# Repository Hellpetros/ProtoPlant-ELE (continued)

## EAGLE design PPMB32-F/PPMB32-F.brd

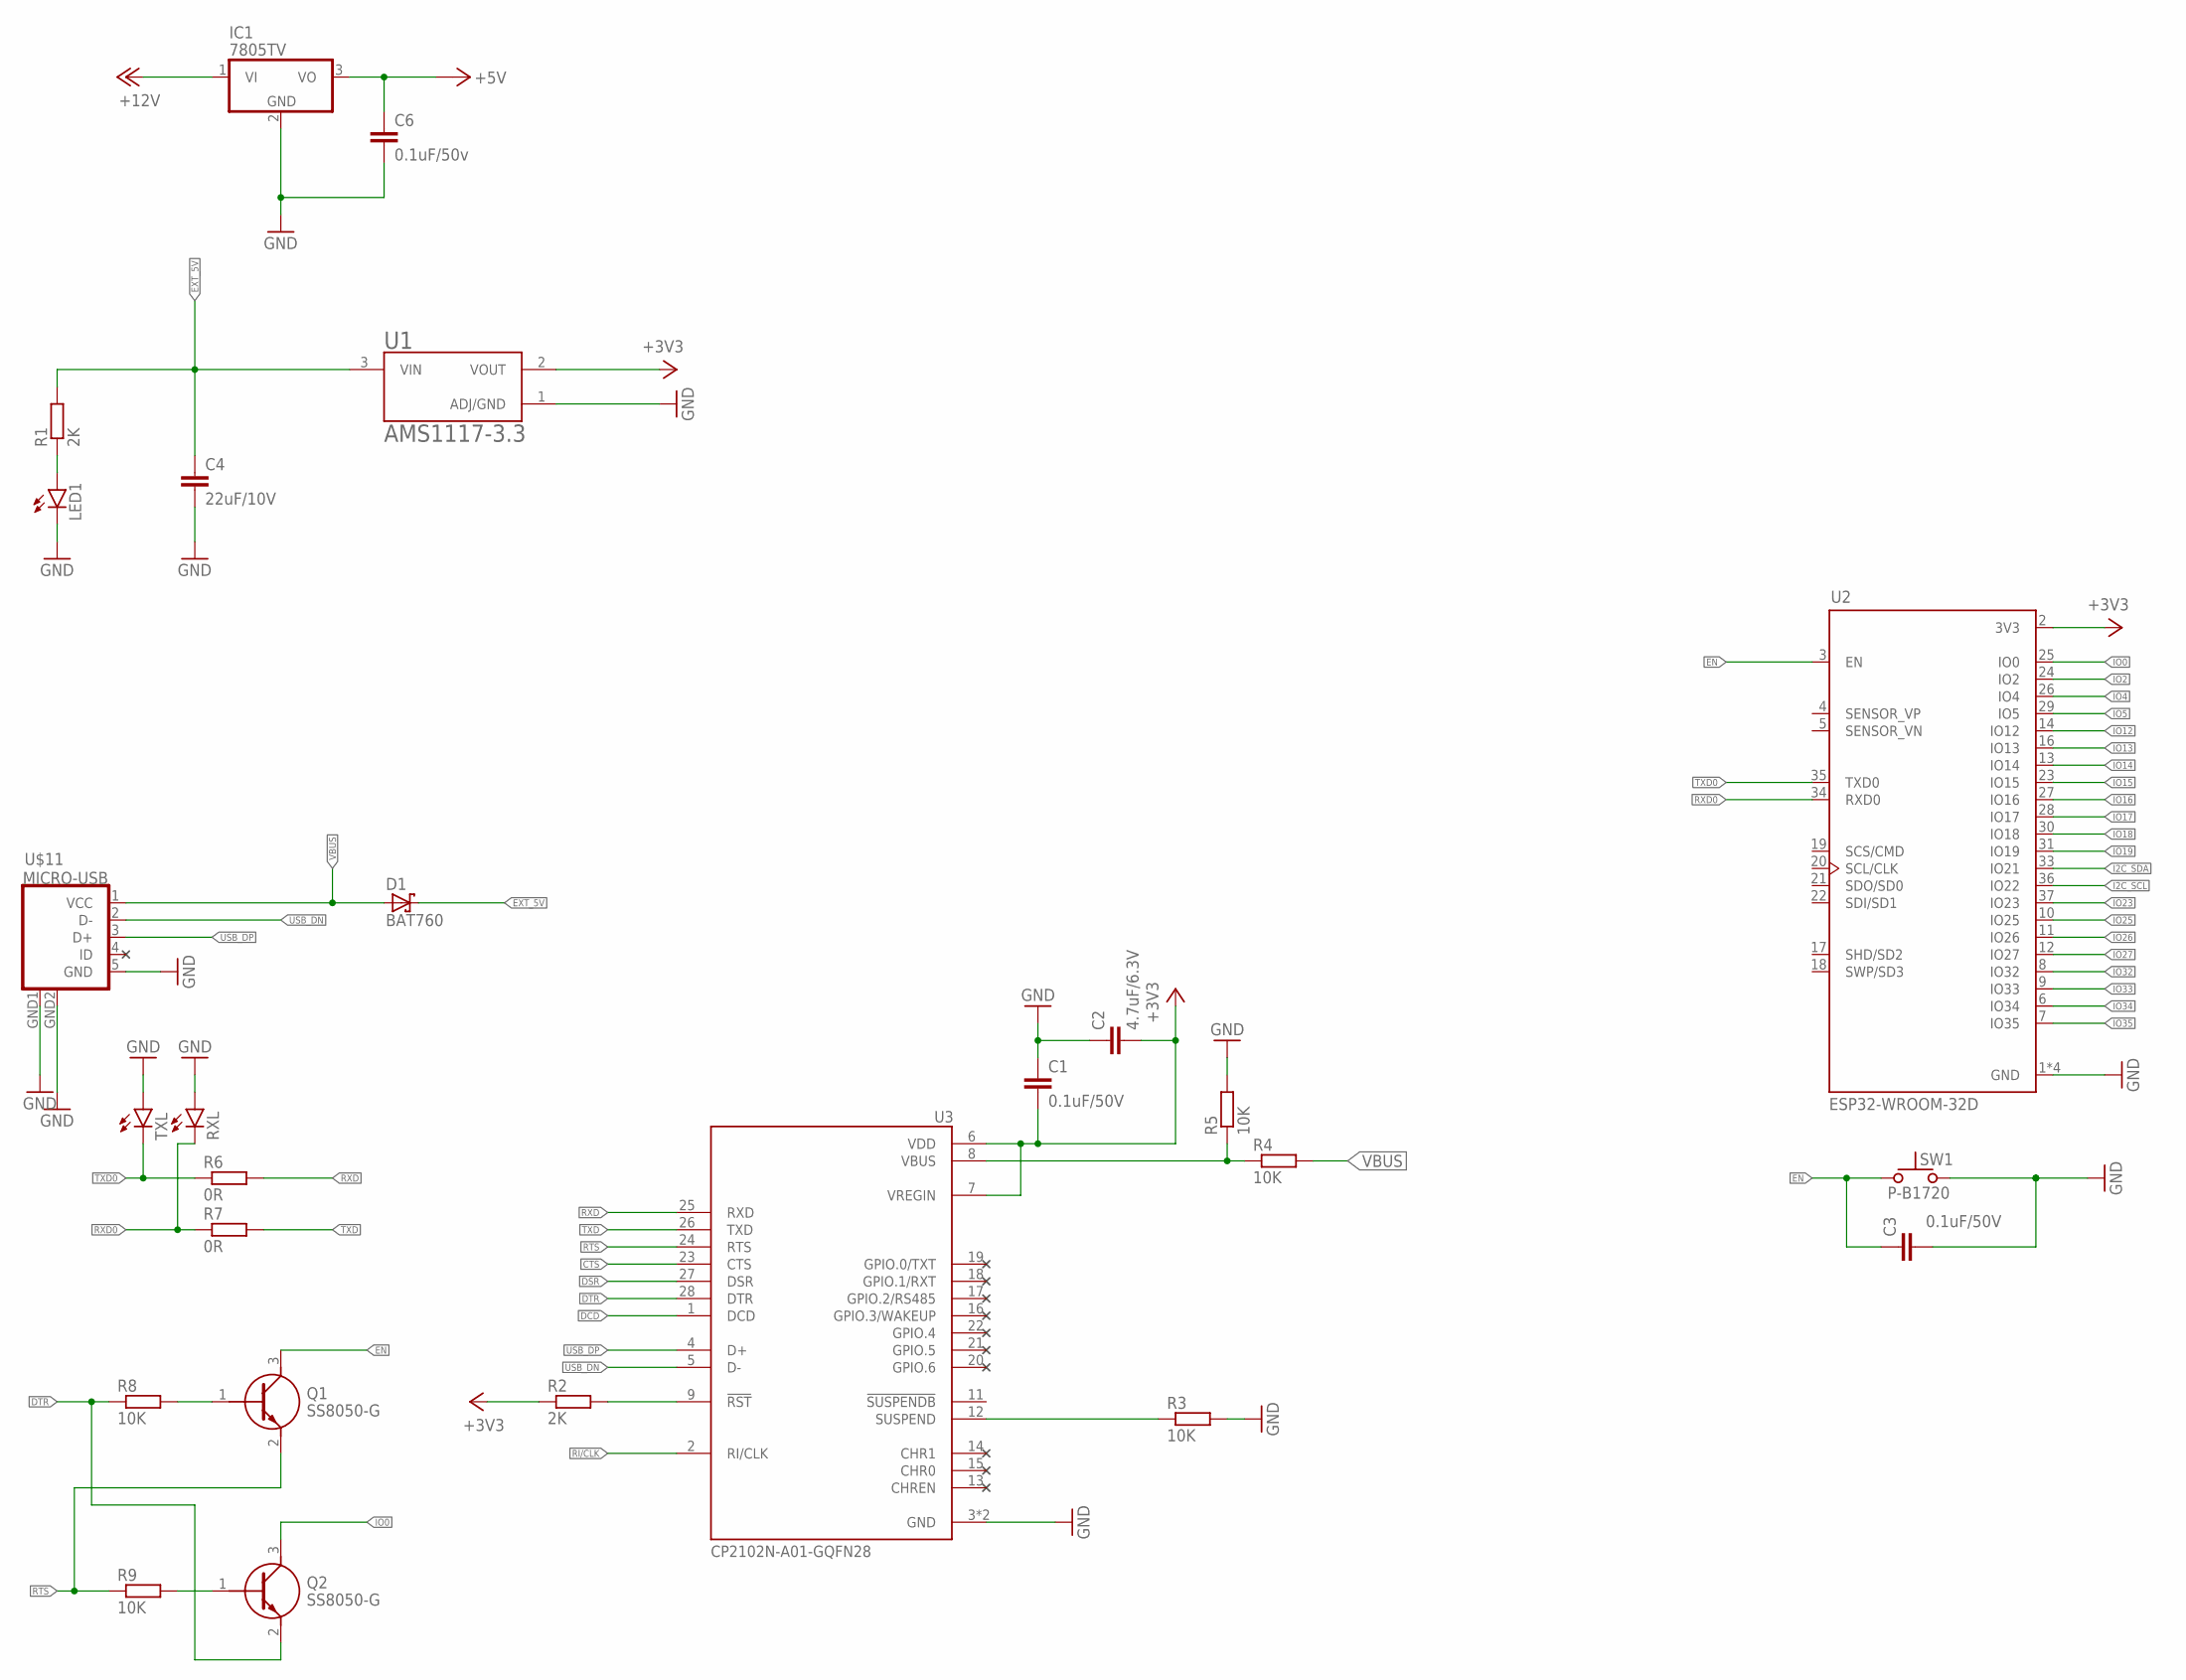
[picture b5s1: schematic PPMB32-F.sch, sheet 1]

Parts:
C1, C3: 0.1uF/50V; C0603
C2: 4.7uF/6.3V; C0603
C4: 22uF/10V; C0603
C6: 0.1uF/50v; C0603
D1: BAT760; SOD323(F)
IC1: 7805TV; TO220V
LED1: LEDCHIP-LED0603; CHIP-LED0603
Q1, Q2: SS8050-G; SOT95P240X115-3N
R1, R2: 2K; R0603
R3, R4, R5, R8, R9: 10K; R0603
R6, R7: 0R; R0603
RXL: LEDCHIP-LED0603; CHIP-LED0603
SW1: P-B1720
TXL: LEDCHIP-LED0603; CHIP-LED0603
U1: AMS1117-3.3; SOT229P700X180-4N
U2: ESP32-WROOM-32D; MODULE_ESP32-WROOM-32D
U3: CP2102N-A01-GQFN28; QFN50P500X500X80-29N
U$11: MICRO-USB

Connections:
+3V3: C1.2, C2.2, R2.1, U1.2 (VOUT), U2.2 (3V3), U3.6 (VDD), U3.7 (VREGIN)
+5V: C6.1, IC1.3 (VO); also elsewhere on the board
+12V: IC1.1 (VI)
CTS: U3.23 (CTS)
DCD: U3.1 (DCD)
DSR: U3.27 (DSR)
DTR: Q2.2 (E), R8.1, U3.28 (DTR)
EN: C3.1, Q1.3 (C), SW1.1, U2.3 (EN)
EXT_5V: C4.1, D1.1 (K), R1.2, U1.3 (VIN); also elsewhere on the board
GND: C1.1, C2.1, C3.2, C4.2, C6.2, IC1.2 (GND), LED1.C, R3.2, R5.2, RXL.A, SW1.2, TXL.A, U1.1 (ADJ/GND), U2.1 (GND), U2.15 (GND), U2.38 (GND), U2.39 (GND), U3.3 (GND), U3.29 (GND), U$11.5 (GND), U$11.GND1 (GND), U$11.GND2 (GND); also elsewhere on the board
I2C_SCL: U2.36 (IO22); also elsewhere on the board
I2C_SDA: U2.33 (IO21); also elsewhere on the board
IO0: Q2.3 (C), U2.25 (IO0)
IO2: U2.24 (IO2)
IO4: U2.26 (IO4)
IO5: U2.29 (IO5)
IO12: U2.14 (IO12)
IO13: U2.16 (IO13)
IO14: U2.13 (IO14)
IO15: U2.23 (IO15)
IO16: U2.27 (IO16)
IO17: U2.28 (IO17)
IO18: U2.30 (IO18)
IO19: U2.31 (IO19)
IO23: U2.37 (IO23)
IO25: U2.10 (IO25)
IO26: U2.11 (IO26)
IO27: U2.12 (IO27)
IO32: U2.8 (IO32)
IO33: U2.9 (IO33)
IO34: U2.6 (IO34)
IO35: U2.7 (IO35)
unnamed: R2.2, U3.9 (!RST)
unnamed: Q1.1 (B), R8.2
unnamed: Q2.1 (B), R9.2
unnamed: LED1.A, R1.1
unnamed: R3.1, U3.12 (SUSPEND)
unnamed: R4.1, R5.1, U3.8 (VBUS)
RI/CLK: U3.2 (RI/CLK)
RTS: Q1.2 (E), R9.1, U3.24 (RTS)
RXD: R6.2, U3.25 (RXD)
RXD0: R7.1, RXL.C, U2.34 (RXD0)
TXD: R7.2, U3.26 (TXD)
TXD0: R6.1, TXL.C, U2.35 (TXD0)
USB_DN: U3.5 (D-), U$11.2 (D-)
USB_DP: U3.4 (D+), U$11.3 (D+)
VBUS: D1.2 (A), R4.2, U$11.1 (VCC)

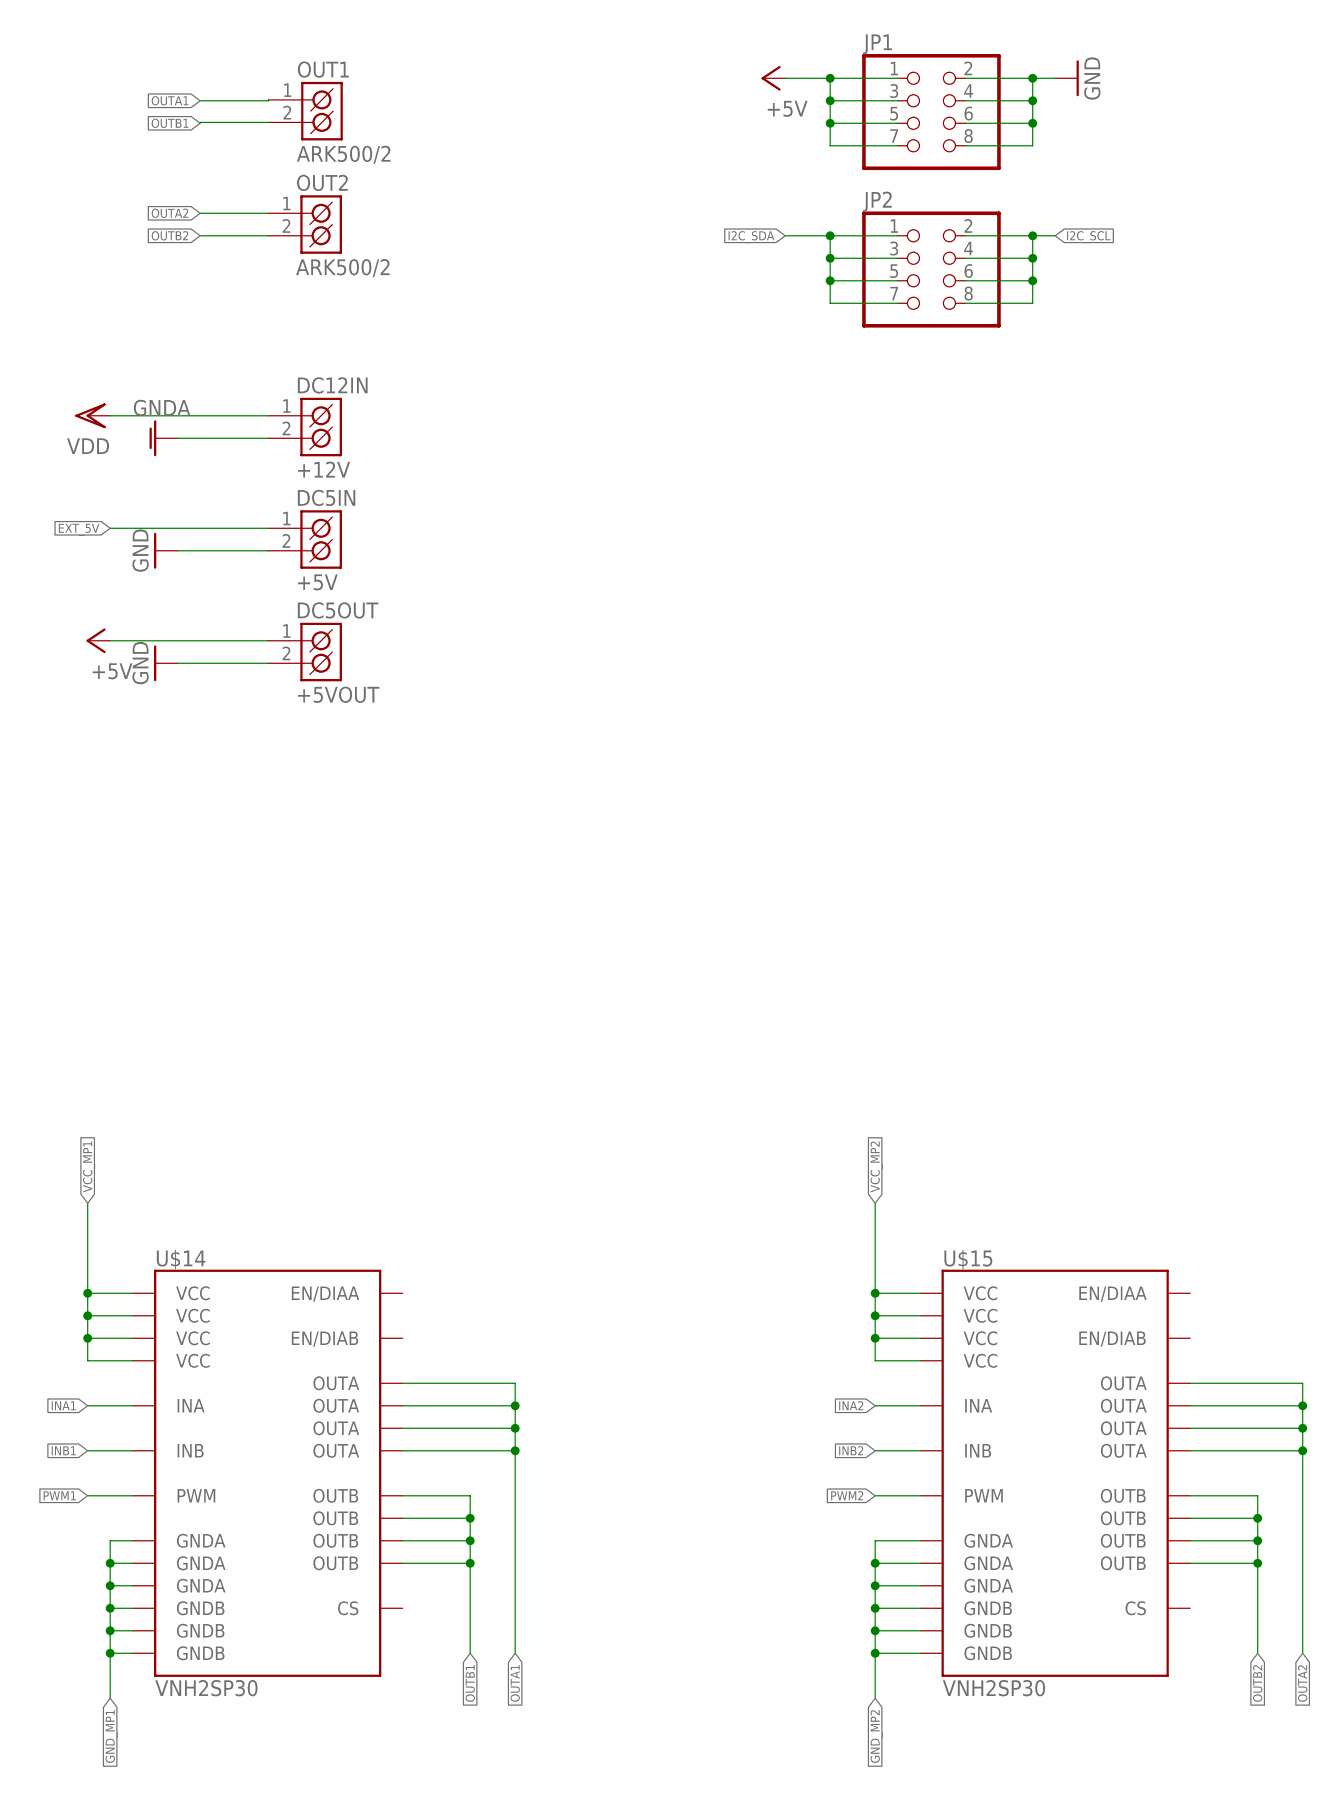
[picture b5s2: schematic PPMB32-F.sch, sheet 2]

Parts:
DC5IN: +5V; ARK500/2
DC5OUT: +5VOUT; ARK500/2
DC12IN: +12V; ARK500/2
JP1, JP2: PINHD-2X4; 2X04
OUT1, OUT2: ARK500/2
U$14, U$15: VNH2SP30

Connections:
+5V: DC5OUT.1 (K1), JP1.1, JP1.3, JP1.5, JP1.7; also elsewhere on the board
EXT_5V: DC5IN.1 (K1); also elsewhere on the board
GND: DC5IN.2 (K2), DC5OUT.2 (K2), JP1.2, JP1.4, JP1.6, JP1.8; also elsewhere on the board
GNDA: DC12IN.2 (K2)
GND_MP1: U$14.18 (GNDB), U$14.19 (GNDB), U$14.20 (GNDB), U$14.26 (GNDA), U$14.27 (GNDA), U$14.28 (GNDA)
GND_MP2: U$15.18 (GNDB), U$15.19 (GNDB), U$15.20 (GNDB), U$15.26 (GNDA), U$15.27 (GNDA), U$15.28 (GNDA)
I2C_SCL: JP2.2, JP2.4, JP2.6, JP2.8; also elsewhere on the board
I2C_SDA: JP2.1, JP2.3, JP2.5, JP2.7; also elsewhere on the board
INA1: U$14.5 (INA)
INA2: U$15.5 (INA)
INB1: U$14.11 (INB)
INB2: U$15.11 (INB)
OUTA1: OUT1.1 (K1), U$14.1 (OUTA), U$14.25 (OUTA), U$14.30 (OUTA), U$14.SLUG3 (OUTA)
OUTA2: OUT2.1 (K1), U$15.1 (OUTA), U$15.25 (OUTA), U$15.30 (OUTA), U$15.SLUG3 (OUTA)
OUTB1: OUT1.2 (K2), U$14.15 (OUTB), U$14.16 (OUTB), U$14.21 (OUTB), U$14.SLUG2 (OUTB)
OUTB2: OUT2.2 (K2), U$15.15 (OUTB), U$15.16 (OUTB), U$15.21 (OUTB), U$15.SLUG2 (OUTB)
PWM1: U$14.8 (PWM)
PWM2: U$15.8 (PWM)
VCC_MP1: U$14.3 (VCC), U$14.13 (VCC), U$14.23 (VCC), U$14.SLUG1 (VCC)
VCC_MP2: U$15.3 (VCC), U$15.13 (VCC), U$15.23 (VCC), U$15.SLUG1 (VCC)
VDD: DC12IN.1 (K1)

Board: 2 copper layers, 35 parts (1 on the bottom side), 31 nets, no tracks yet.

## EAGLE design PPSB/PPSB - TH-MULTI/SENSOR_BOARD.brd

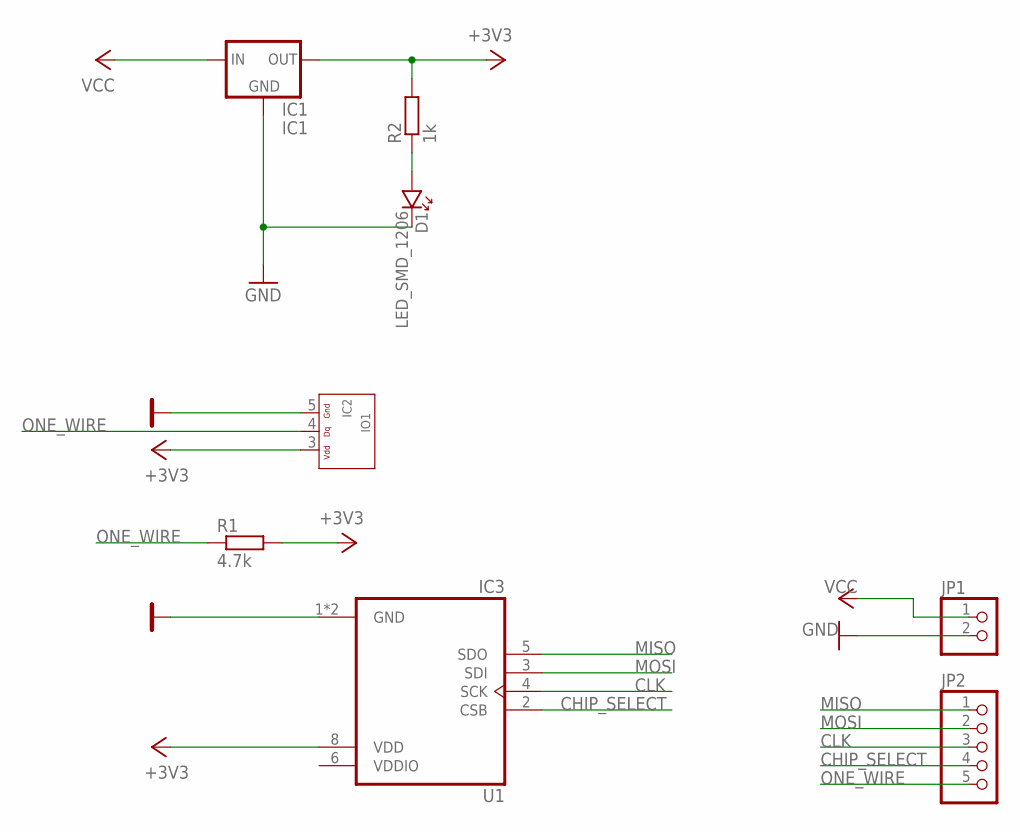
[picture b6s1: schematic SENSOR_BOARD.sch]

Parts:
D1: LED_SMD_1206; P1206
IC1: IC1; SOT223
IO1: IC2; SO08
JP1: PINHD-1X2; 1X02
JP2: PINHD-1X5; 1X05
R1: 4.7k; R0603
R2: 1k; R0603
U1: IC3; PSON65P250X250X100-8N

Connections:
+3V3: IC1.2 (OUT), IC1.4 (OUT), IO1.3 (+VCC), R1.2, R2.2, U1.8 (VDD)
CHIP_SELECT: JP2.4, U1.2 (CSB)
CLK: JP2.3, U1.4 (SCK)
GND: D1.K, IC1.1 (GND), IO1.5 (GND), JP1.2, U1.1 (GND), U1.7 (GND)
MISO: JP2.1, U1.5 (SDO)
MOSI: JP2.2, U1.3 (SDI)
unnamed: D1.A, R2.1
ONE_WIRE: IO1.4 (1WIRE), JP2.5, R1.1
VCC: IC1.3 (IN), JP1.1
VDDIO: U1.6 (VDDIO)

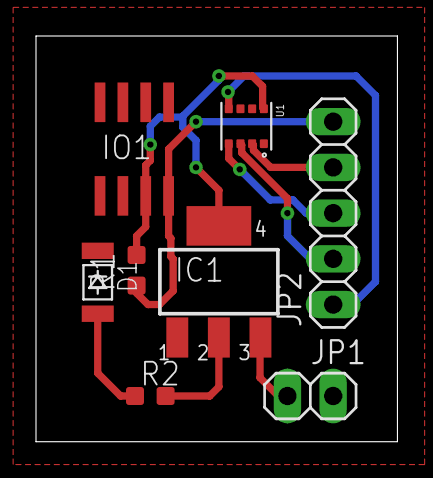
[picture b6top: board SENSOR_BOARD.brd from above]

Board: 2 copper layers, 20.1 x 22.5 mm, 8 parts (0 on the bottom side), 9 nets.

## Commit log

2020-02-01 Commit initial state of files, edit .gitignore
2020-02-01 Made major advances in PPMB32-E scheme. Started routing PPMB32-E
2020-02-02 Made progress on PPMB32-E scheme and board. Minor fixes in PPMB32-F board
2020-02-02 Progress on routing PPMB32-E
2020-02-10 Major changes in PPMB32-E board and scheme
2020-02-10 Rebuilt PPSB folder tree; finish PPSB-T
2020-02-10 Add PPSB-TH scheme.
2020-02-10 Finish PPSB-TH
2020-02-10 Add pins connected to remaining GPIOs on ESP32devkitC
2020-02-11 Edit silkscreen on PPMB32-E
2020-02-18 Edit PPMB32-E; prepare PPSB-T for sending gerbers to JLCPCB
2020-02-22 Create LICENCE
2020-03-02 Add PanelBoard
2020-04-18 PanelBoard layout reworked
2020-04-18 Backlink to CADLAB.io has been added.
2020-04-21 Changed PPMB32-E scheme layout
2020-04-21 First development version of PPMB32-E
2020-04-21 Cleanup
2020-04-21 Minor fix
2020-05-01 Remove obsolete files, pre-release versions of PPSB-T & PPSB-TH
2020-05-01 Fixed board outline
2020-05-05 Improved schematics layout.
2020-05-05 Update schematics
